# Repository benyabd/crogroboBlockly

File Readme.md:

# Blockly based robot to comunicate with apps
# google blockly https://github.com/google/blockly-android
# ardublocklydroid https://github.com/suriyanath/ArduBlocklyDroid
# robo blockly creation lofiblocks.com/diy
#

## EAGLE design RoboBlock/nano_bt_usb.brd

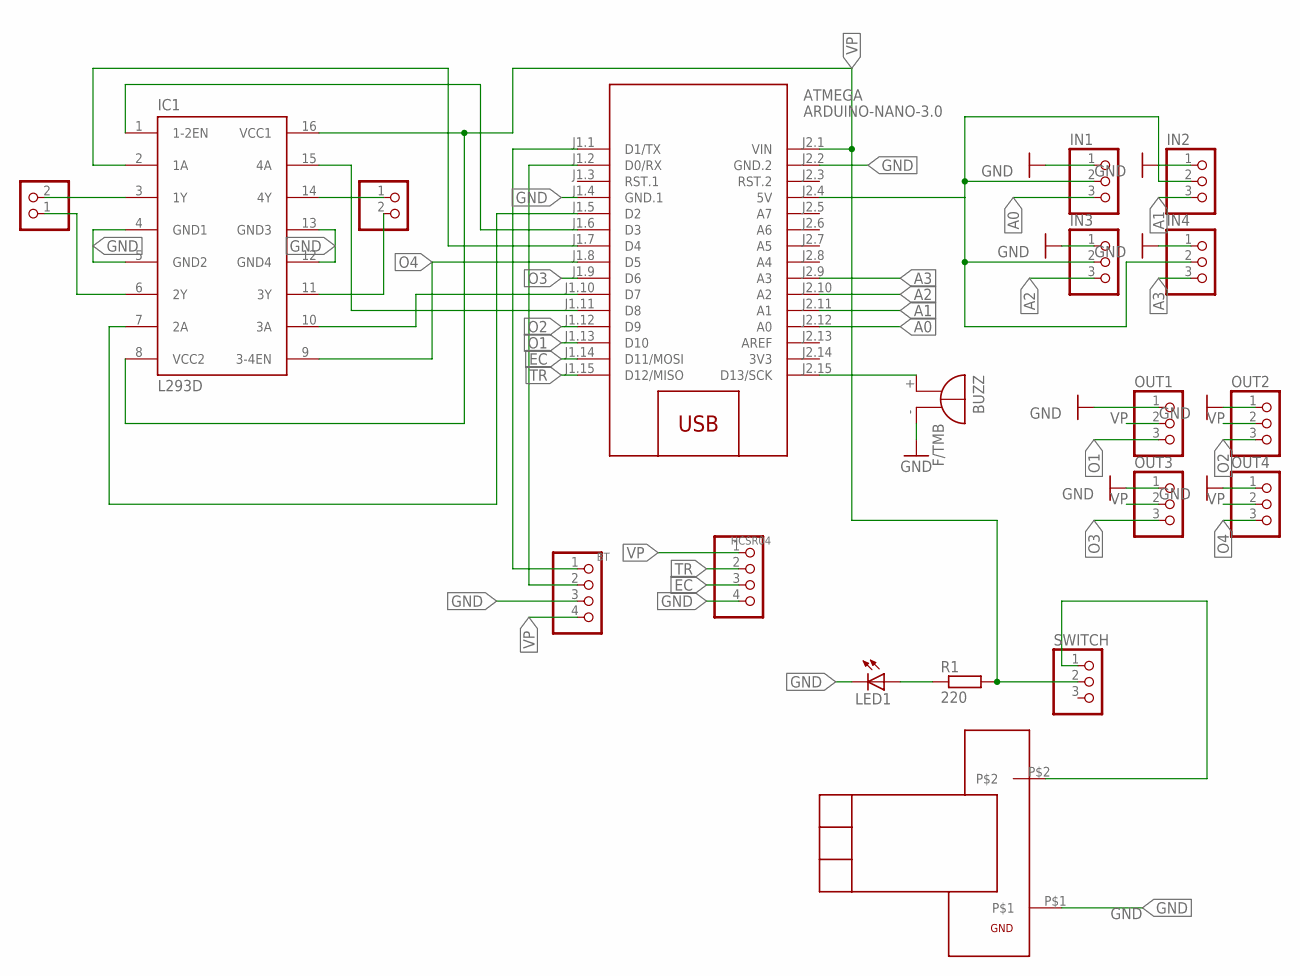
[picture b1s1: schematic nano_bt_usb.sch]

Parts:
ATMEGA: ARDUINO-NANO-3.0
BT: PINHD-1X4; 1X04
BUZZ: F/TMB
HCSR04: PINHD-1X4; 1X04
IC1: L293D; DIL16
IN1, IN2, IN3, IN4: PINHD-1X3; 1X03
LED1: LED3MM
MT1, MT2: PINHD-1X2; 1X02
OUT1, OUT2, OUT3, OUT4: PINHD-1X3; 1X03
R1: 220; 0204/7
SWITCH: PINHD-1X3; 1X03
U$1: MICROUSBMODUL; MICROUSB

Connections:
3V3: ATMEGA.J2.14 (3V3)
A0: ATMEGA.J2.12 (A0), IN1.3
A1: ATMEGA.J2.11 (A1), IN2.3
A2: ATMEGA.J2.10 (A2), IN3.3
A3: ATMEGA.J2.9 (A3), IN4.3
EC: ATMEGA.J1.14 (D11/MOSI), HCSR04.3
GND: ATMEGA.J1.4 (GND.1), ATMEGA.J2.2 (GND.2), BT.3, BUZZ.-, HCSR04.4, IC1.4 (GND1), IC1.5 (GND2), IC1.12 (GND4), IC1.13 (GND3), IN1.1, IN2.1, IN3.1, IN4.1, LED1.K (C), OUT1.1, OUT2.1, OUT3.1, OUT4.1, U$1.P$1
unnamed: IC1.3 (1Y), MT1.2
unnamed: IC1.6 (2Y), MT1.1
unnamed: IC1.14 (4Y), MT2.1
unnamed: IC1.11 (3Y), MT2.2
unnamed: ATMEGA.J1.1 (D1/TX), BT.1
unnamed: ATMEGA.J1.2 (D0/RX), BT.2
unnamed: ATMEGA.J2.15 (D13/SCK), BUZZ.+
unnamed: ATMEGA.J1.5 (D2), IC1.7 (2A)
unnamed: ATMEGA.J1.6 (D3), IC1.1 (1-2EN)
unnamed: ATMEGA.J1.7 (D4), IC1.2 (1A)
unnamed: SWITCH.1, U$1.P$2
unnamed: ATMEGA.J1.10 (D7), IC1.10 (3A)
unnamed: ATMEGA.J1.11 (D8), IC1.15 (4A)
unnamed: LED1.A, R1.1
unnamed: ATMEGA.J2.4 (5V), IN1.2, IN2.2, IN3.2, IN4.2
O1: ATMEGA.J1.13 (D10), OUT1.3
O2: ATMEGA.J1.12 (D9), OUT2.3
O3: ATMEGA.J1.9 (D6), OUT3.3
O4: ATMEGA.J1.8 (D5), IC1.9 (3-4EN), OUT4.3
TR: ATMEGA.J1.15 (D12/MISO), HCSR04.2
VP: ATMEGA.J2.1 (VIN), BT.4, HCSR04.1, IC1.8 (VCC2), IC1.16 (VCC1), OUT1.2, OUT2.2, OUT3.2, OUT4.2, R1.2, SWITCH.2

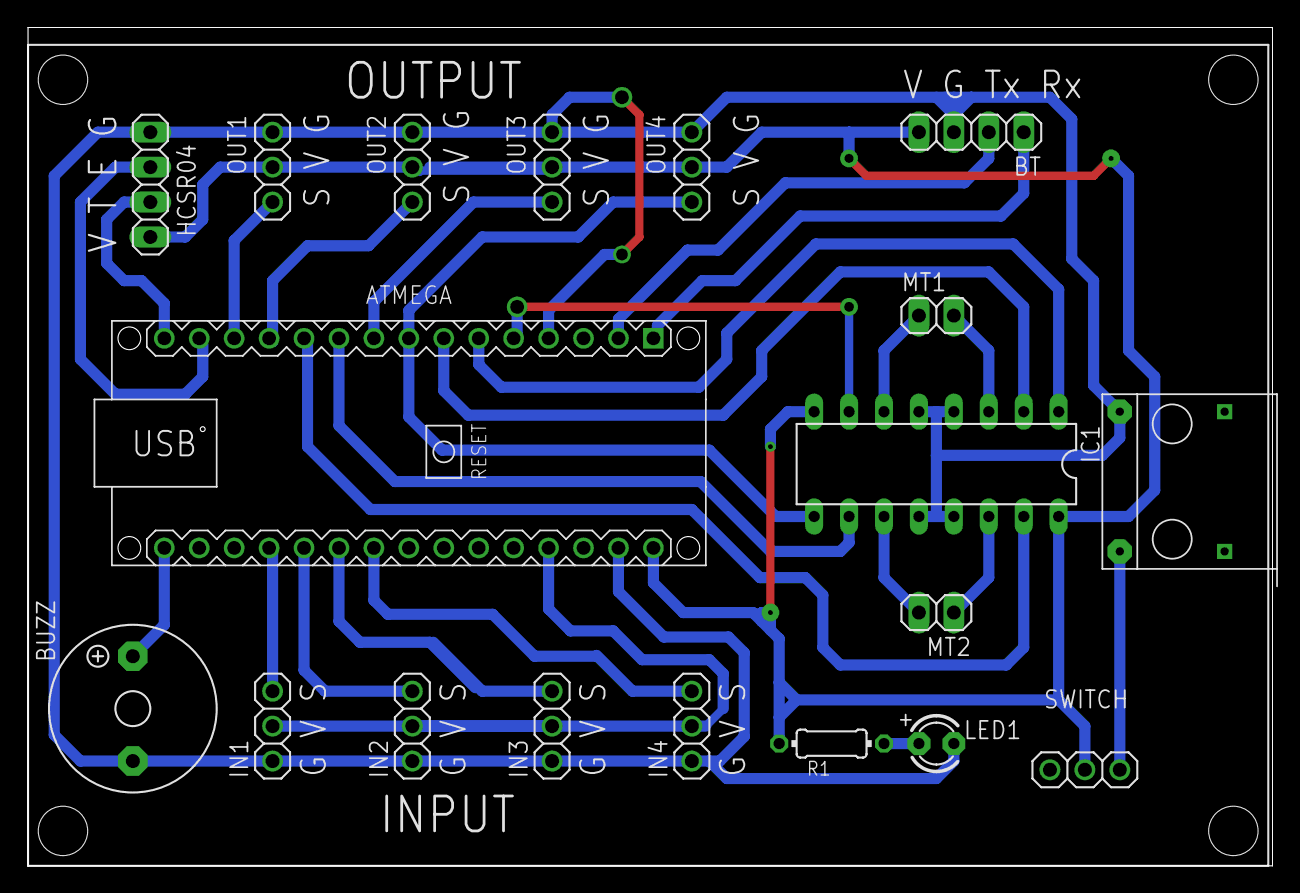
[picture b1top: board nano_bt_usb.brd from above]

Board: 2 copper layers, 90.4 x 60.9 mm, 19 parts (0 on the bottom side), 27 nets.

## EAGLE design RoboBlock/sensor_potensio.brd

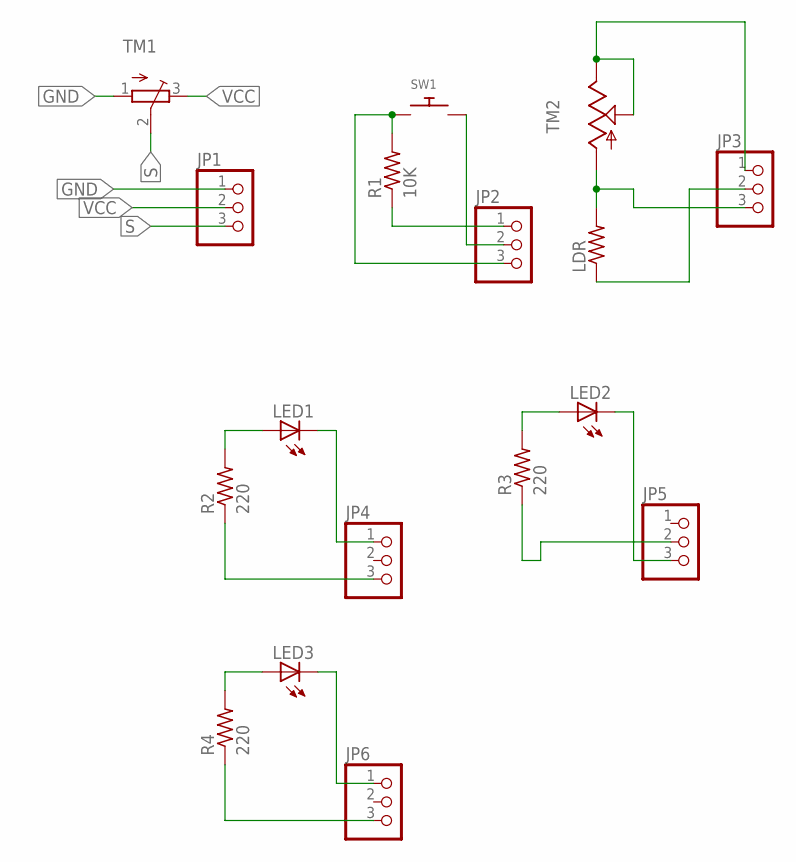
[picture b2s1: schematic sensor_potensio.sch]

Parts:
JP1, JP2, JP3, JP4, JP5, JP6: PINHD-1X3; 1X03
LDR: R-US_0204/5; 0204/5
LED1, LED2, LED3: LED5MM
R1: 10K; 0207/7
R2, R3, R4: 220; 0207/7
SW1: SWITCH_PUSHBUTTONEVQ-PE; TACT_PANA-EVQ
TM1: TRIMPOT3386; TRIM-3386
TM2: TRIM; 6MM

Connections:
GND: JP1.1, TM1.1 (A)
unnamed: JP2.3, R1.2, SW1.P$1
unnamed: JP2.1, R1.1
unnamed: JP2.2, SW1.P$2
unnamed: JP3.3, LDR.2, TM2.A
unnamed: JP3.1, TM2.E, TM2.S
unnamed: JP3.2, LDR.1
unnamed: LED1.A, R2.2
unnamed: JP4.3, R2.1
unnamed: JP4.1, LED1.K (C)
unnamed: LED2.A, R3.2
unnamed: JP5.2, R3.1
unnamed: LED3.A, R4.2
unnamed: JP5.3, LED2.K (C)
unnamed: JP6.3, R4.1
unnamed: JP6.1, LED3.K (C)
S: JP1.3, TM1.2 (S)
VCC: JP1.2, TM1.3 (E)

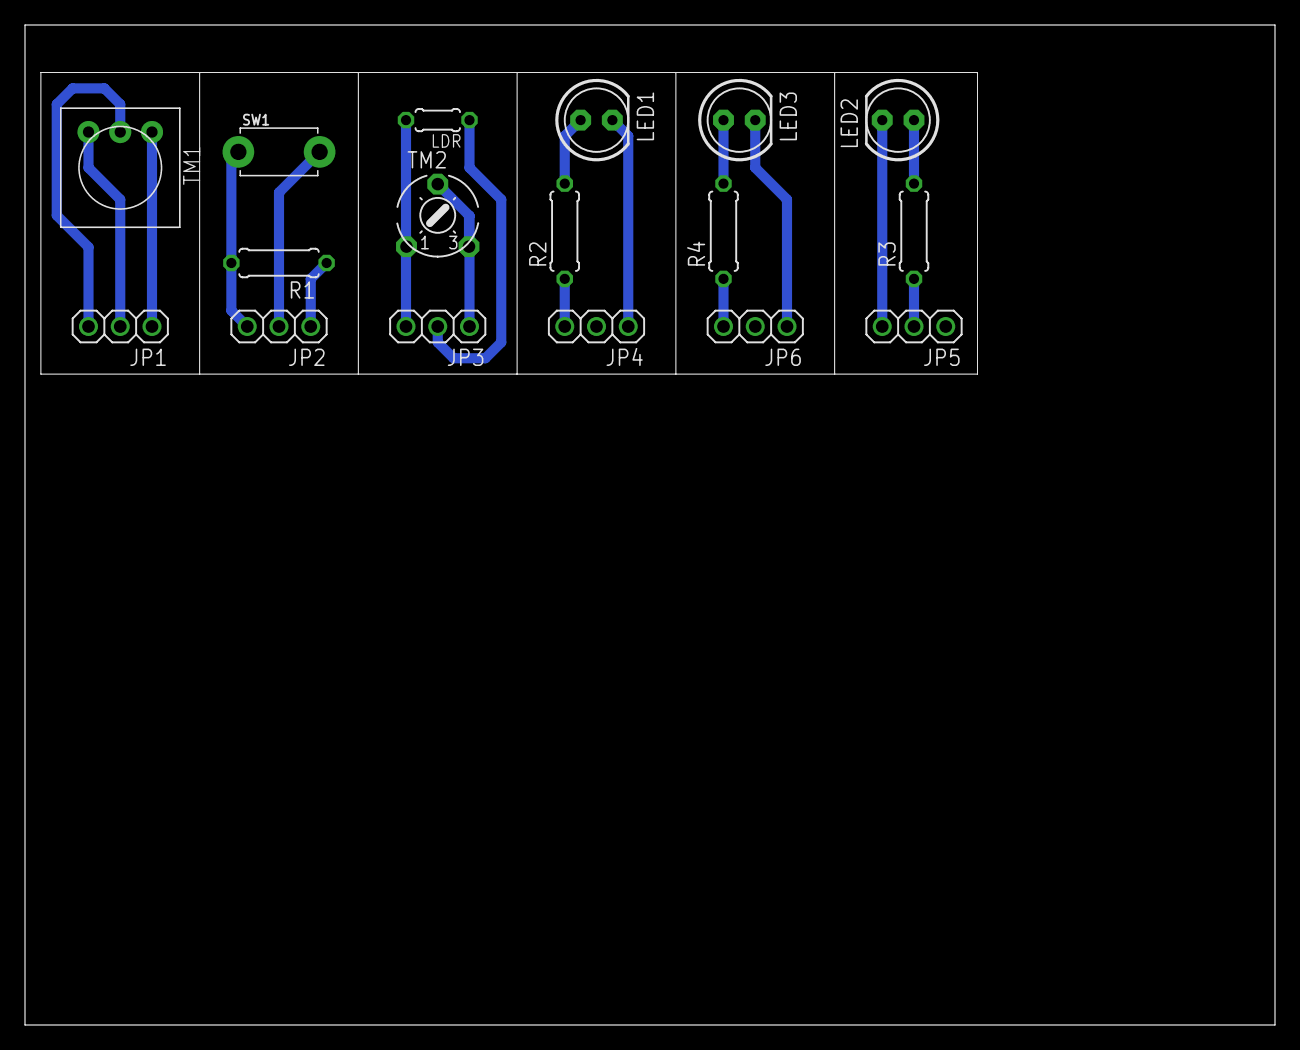
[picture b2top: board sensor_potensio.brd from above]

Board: 2 copper layers, 100.0 x 80.0 mm, 17 parts (0 on the bottom side), 18 nets.

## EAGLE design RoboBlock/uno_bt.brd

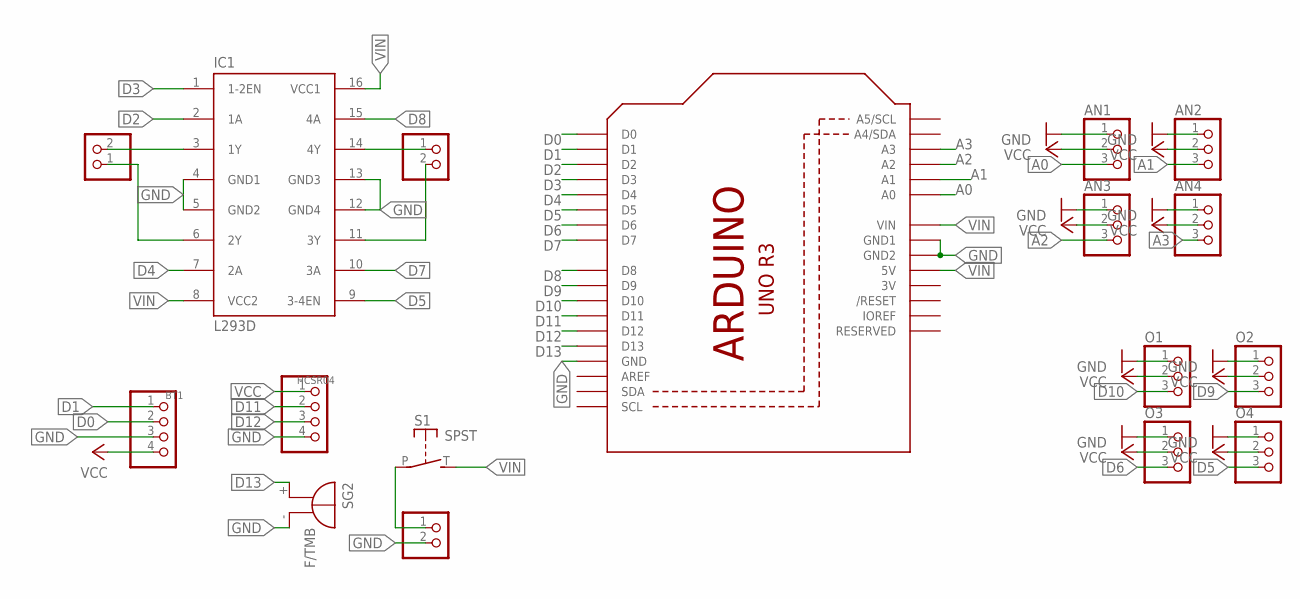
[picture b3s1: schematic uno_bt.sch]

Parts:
AN1, AN2, AN3, AN4: PINHD-1X3; 1X03
BT1: PINHD-1X4; 1X04
DCIN: PINHD-1X2; 1X02
HCSR04: PINHD-1X4; 1X04
IC1: L293D; DIL16
MT1, MT2: PINHD-1X2; 1X02
O1, O2, O3, O4: PINHD-1X3; 1X03
S1: SPST; JUDCOSPST
SG2: F/TMB
U1: ARDUINOR3-BPLACE

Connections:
3V: U1.3V
A0: AN1.3, U1.A0
A1: AN2.3, U1.A1
A2: AN3.3, U1.A2
A3: AN4.3, U1.A3
D0: BT1.2, U1.D0
D1: BT1.1, U1.D1
D2: IC1.2 (1A), U1.D2
D3: IC1.1 (1-2EN), U1.D3
D4: IC1.7 (2A), U1.D4
D5: IC1.9 (3-4EN), O4.3, U1.D5
D6: O3.3, U1.D6
D7: IC1.10 (3A), U1.D7
D8: IC1.15 (4A), U1.D8
D9: O2.3, U1.D9
D10: O1.3, U1.D10
D11: HCSR04.2, U1.D11
D12: HCSR04.3, U1.D12
D13: SG2.+, U1.D13
GND: AN1.1, AN2.1, AN3.1, AN4.1, BT1.3, DCIN.2, HCSR04.4, IC1.4 (GND1), IC1.5 (GND2), IC1.12 (GND4), IC1.13 (GND3), O1.1, O2.1, O3.1, O4.1, SG2.-, U1.GND, U1.GND1, U1.GND2
unnamed: IC1.3 (1Y), MT1.2
unnamed: IC1.6 (2Y), MT1.1
unnamed: IC1.14 (4Y), MT2.1
unnamed: IC1.11 (3Y), MT2.2
unnamed: DCIN.1, S1.P
VCC: AN1.2, AN2.2, AN3.2, AN4.2, BT1.4, HCSR04.1, O1.2, O2.2, O3.2, O4.2
VIN: IC1.8 (VCC2), IC1.16 (VCC1), S1.T (S), U1.5V, U1.VIN

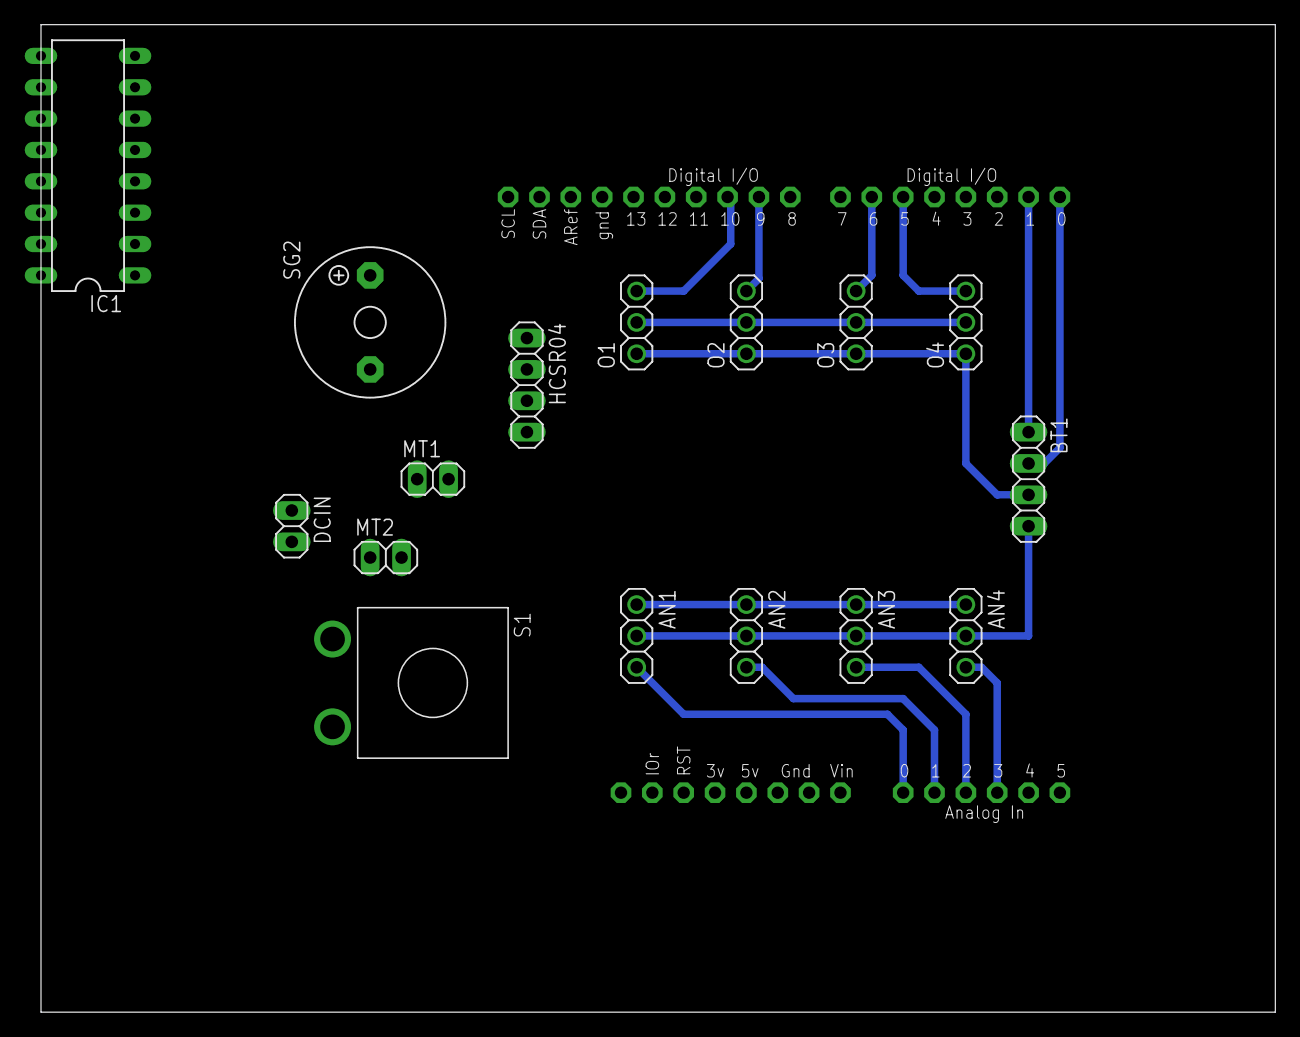
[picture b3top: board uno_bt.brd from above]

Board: 2 copper layers, 100.0 x 80.0 mm, 17 parts (0 on the bottom side), 26 nets.

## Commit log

2020-06-22 file awal
2020-06-23 important notes
2020-06-24 desain skema dan pcb
2020-06-25 sensor
2020-07-15 printout pcb

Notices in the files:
parts and their libraries:
diy-modules: Released under the Creative Commons Attribution 4.0 International License: http://creativecommons.org/licenses/by/4.0
